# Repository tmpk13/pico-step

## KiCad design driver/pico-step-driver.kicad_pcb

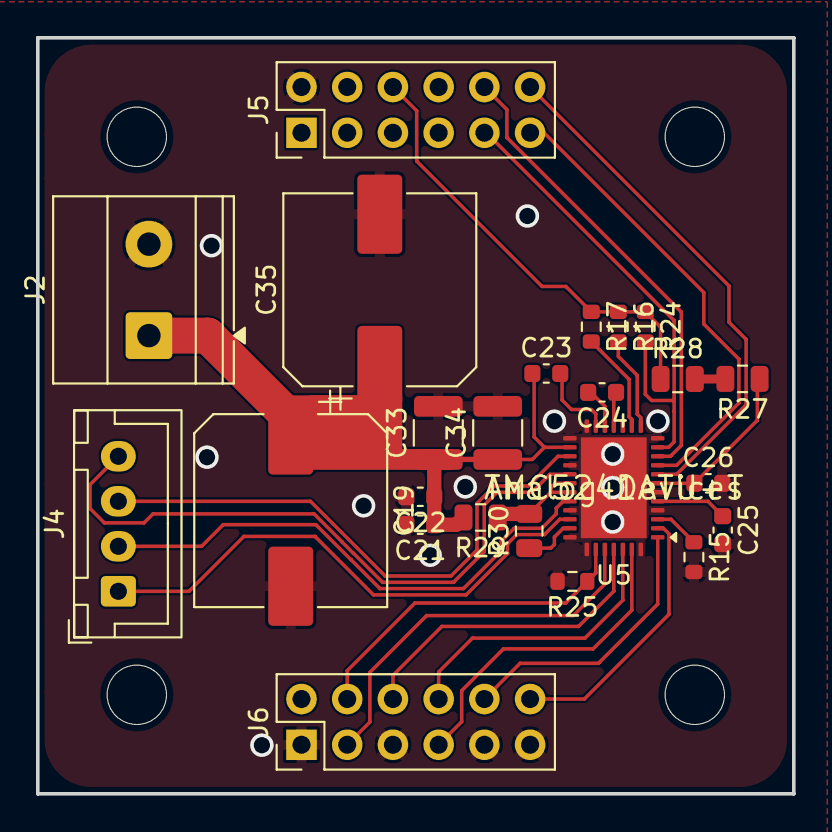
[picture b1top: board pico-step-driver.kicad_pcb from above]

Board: 4 copper layers, 42.0 x 42.0 mm, 24 parts (0 on the bottom side), 25 nets.

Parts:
C19, C35: 100u 63V; CP_Elec_10x10.5
C21, C22: 100n 100V; C_0603_1608Metric
C23: 1u 25V; C_0603_1608Metric
C24: 22n 100V; C_0603_1608Metric
C25: 2.2u; C_0603_1608Metric
C26: 100n; C_0603_1608Metric
C33, C34: 2.2u 100V; C_1210_3225Metric
J2: VM; TerminalBlock_Phoenix_MKDS-1,5-2-5.08_1x02_P5.08mm_Horizont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
J4: Motor; JST_XH_B4B-XH-A_1x04_P2.50mm_Vertical
J5, J6: Stack 2x06; PinHeader_2x06_P2.54mm_Vertical
R15: 12k; R_0603_1608Metric
R16, R17, R24, R25: 10k; R_0603_1608Metric
R27, R28, R29, R30: 0; C_0805_2012Metric
U5: TMC5241; ADI_TQFN-38-1EP_5x7mm_P0.5mm_EP3.65x5.6mm_ThermalVias

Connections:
+3V3: C26.1, J5.6, R16.1, R17.1, R24.1, R27.1, R27.2, R28.1, R28.2, U5.7 (VCC_IO)
/driver/OUT1A: J4.1, U5.29 (OUT1A)
/driver/OUT1B: J4.3, U5.22 (OUT1B)
/driver/OUT2A: J4.2, U5.27 (OUT2A)
/driver/OUT2B: J4.4, U5.24 (OUT2B)
ENC_IFA: J5.10, U5.10 (ENCA)
ENC_IFB: J5.11, U5.9 (ENCB)
ENC_IFC: J5.12, U5.8 (ENCN)
GND: C19.2, C21.2, C22.2, C25.2, C26.2, C33.2, C34.2, C35.2, J2.2, J5.2, J6.1, J6.5, J6.9, J6.11, R15.2, R25.2, U5.4 (AIN), U5.6 (AGND), U5.12 (UART_EN), U5.19 (NC), U5.20 (NC), U5.23 (PGND), U5.28 (PGND), U5.31 (NC), U5.32 (NC), U5.38 (CLK), U5.39 (EP)
unnamed: C24.1, U5.16 (CPI)
unnamed: C24.2, U5.17 (CPO)
unnamed: R16.2, U5.13 (DIAG0)
unnamed: R17.2, U5.14 (DIAG1_SW)
unnamed: R15.1, U5.3 (IREF)
unnamed: C23.2, U5.18 (VCP)
unnamed: C25.1, U5.5 (VDD1V8)
TMC_CSN: J6.3, U5.34 (CSN_AD2)
TMC_ENN: J5.9, R24.2, U5.11 (DRV_ENN)
TMC_REFL: J6.10, U5.1 (REFL)
TMC_REFR: J6.12, U5.2 (REFR)
TMC_SCK: J6.6, U5.35 (SCK_AD1)
TMC_SDI: J6.8, U5.36 (SDI_AD0)
TMC_SDO: J6.7, U5.37 (SDO_NAO)
TMC_SLEEPN: J6.4, R25.1, U5.33 (nSLEEP)
VM: C19.1, C21.1, C22.1, C23.1, C33.1, C34.1, C35.1, J2.1, R29.1, R29.2, R30.1, R30.2, U5.21 (VS), U5.25 (VS), U5.26 (VS), U5.30 (VS)
